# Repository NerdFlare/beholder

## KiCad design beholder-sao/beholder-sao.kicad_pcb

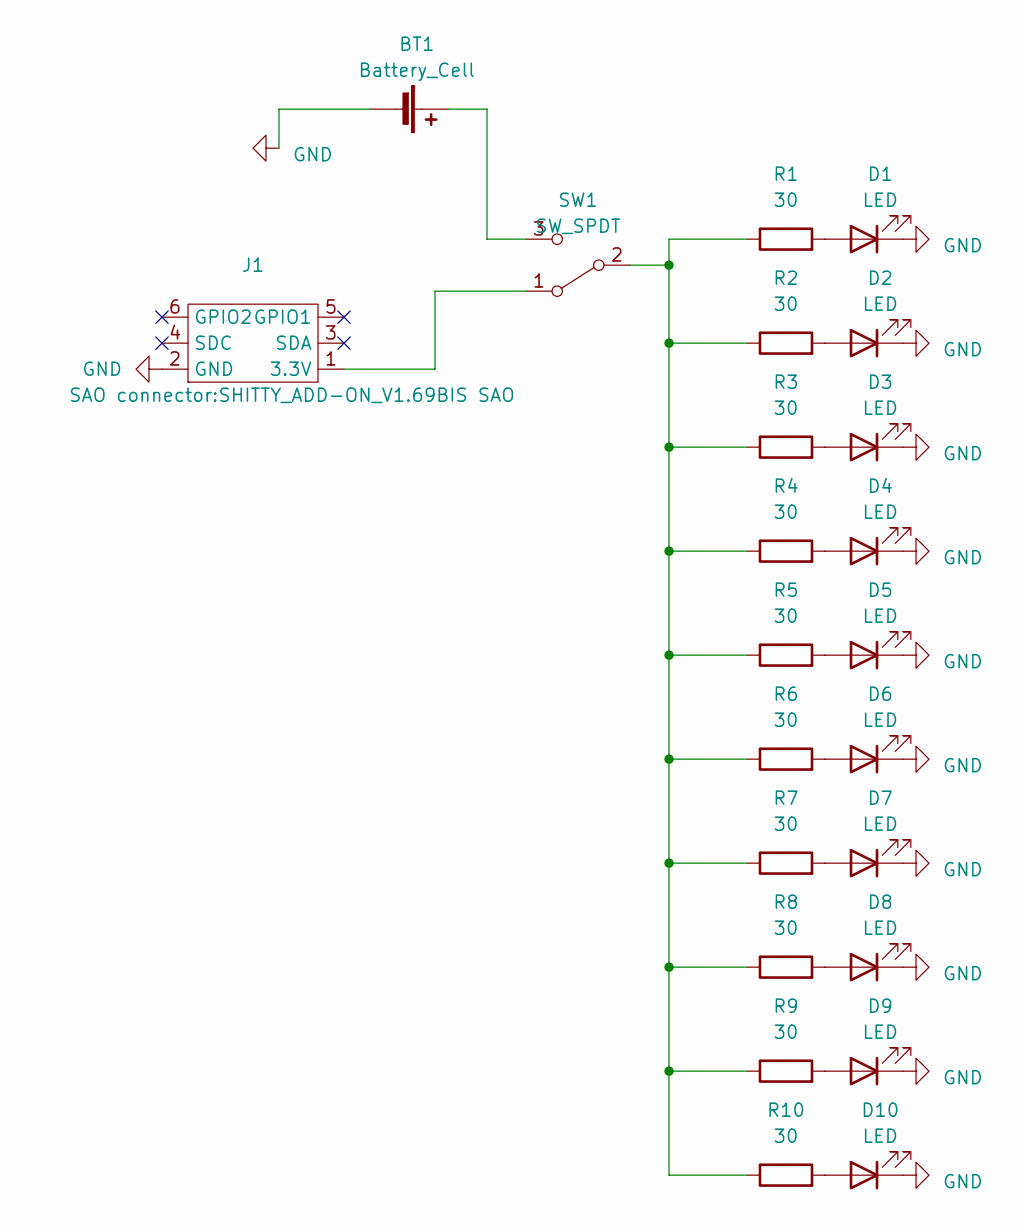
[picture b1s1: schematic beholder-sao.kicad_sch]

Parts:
BT1: Battery_Cell; BatteryHolder_Keystone_3034_1x20mm
D1, D2, D3, D4, D5, D6, D7, D8, D9, D10: LED; LED_D5.0mm
J1: SHITTY_ADD-ON_V1.69BIS SAO
R1, R2, R3, R4, R5, R6, R7, R8, R9, R10: 30; R_1206_3216Metric_Pad1.30x1.75mm_HandSolder
SW1: SW_SPDT; SW_SPDT_PCM12

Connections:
GND: BT1.2 (-), D1.1 (K), D2.1 (K), D3.1 (K), D4.1 (K), D5.1 (K), D6.1 (K), D7.1 (K), D8.1 (K), D9.1 (K), D10.1 (K), J1.2 (GND)
unnamed: BT1.1 (+), SW1.3 (C)
unnamed: D1.2 (A), R1.2
unnamed: D2.2 (A), R2.2
unnamed: D3.2 (A), R3.2
unnamed: D4.2 (A), R4.2
unnamed: D5.2 (A), R5.2
unnamed: D6.2 (A), R6.2
unnamed: D7.2 (A), R7.2
unnamed: D8.2 (A), R8.2
unnamed: D9.2 (A), R9.2
unnamed: D10.2 (A), R10.2
unnamed: J1.1 (3.3V), SW1.1 (A)
unnamed: R1.1, R2.1, R3.1, R4.1, R5.1, R6.1, R7.1, R8.1, R9.1, R10.1, SW1.2 (B)

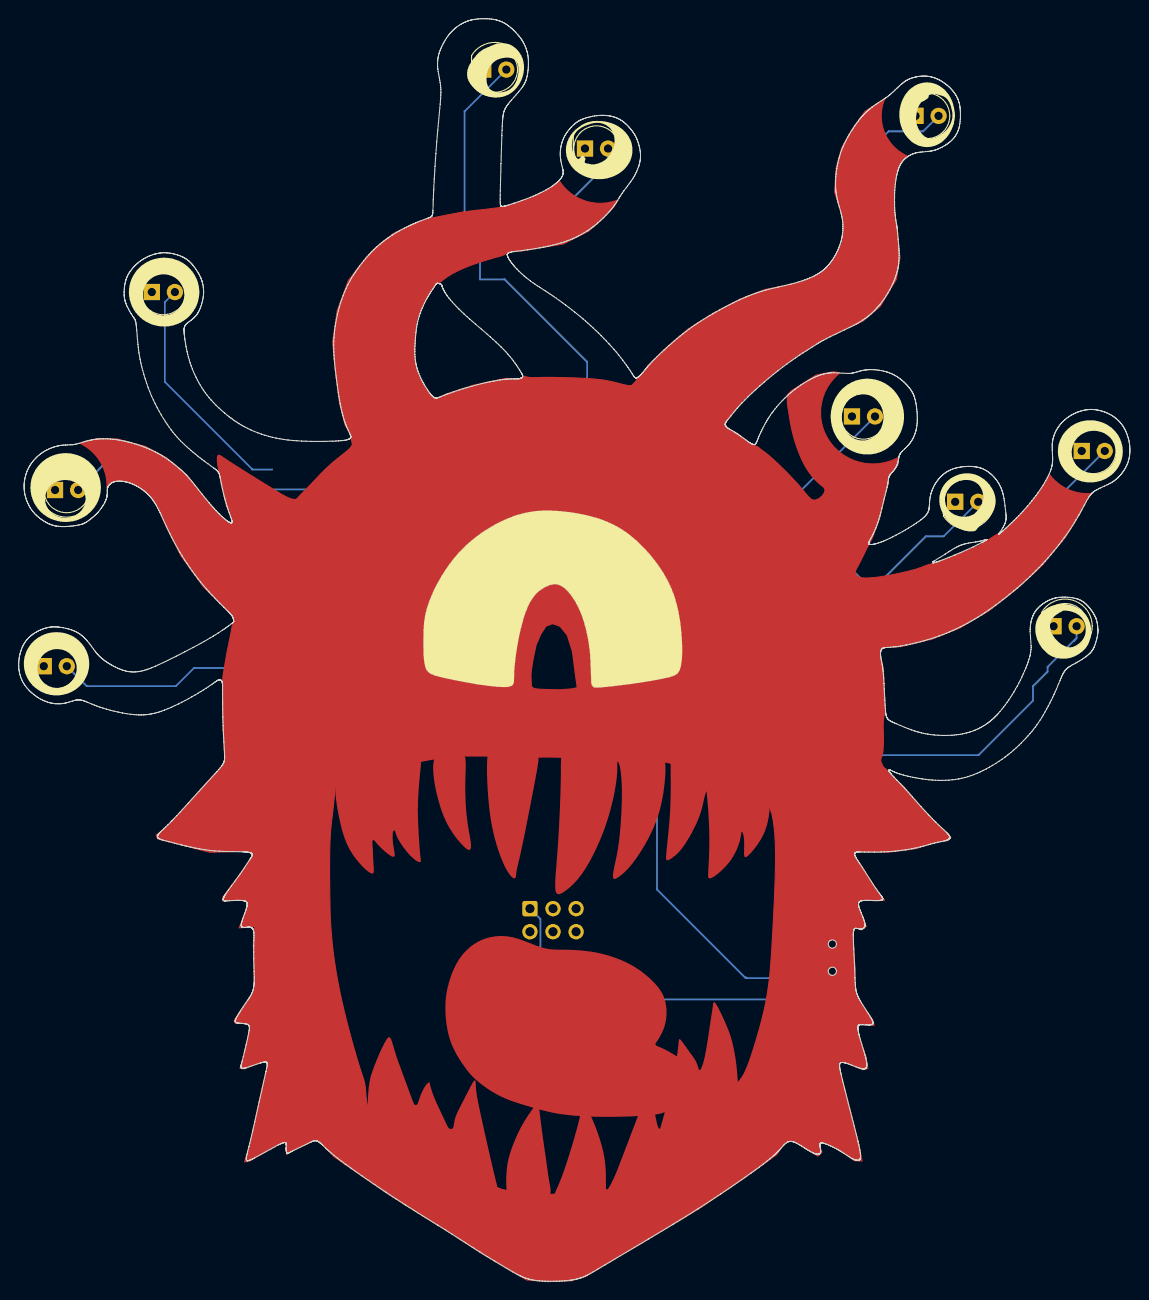
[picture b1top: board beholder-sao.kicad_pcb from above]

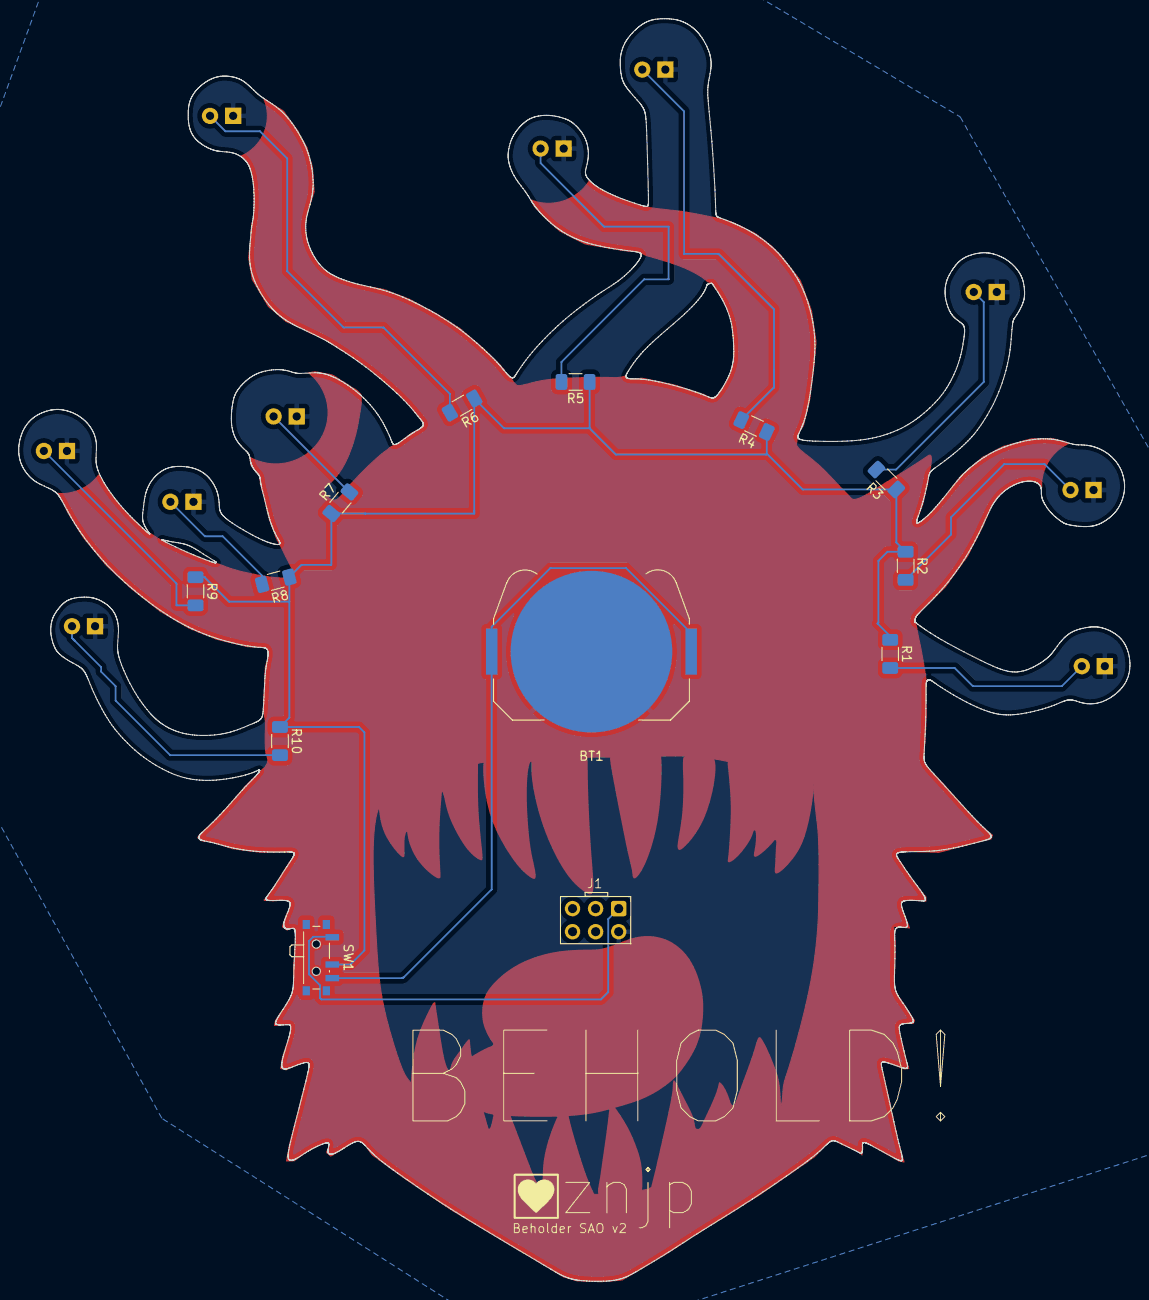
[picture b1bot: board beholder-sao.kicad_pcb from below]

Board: 2 copper layers, 122.4 x 139.0 mm, 23 parts (13 on the bottom side), 14 nets.

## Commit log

2025-01-15 Initial commit of the beholder badge project.
